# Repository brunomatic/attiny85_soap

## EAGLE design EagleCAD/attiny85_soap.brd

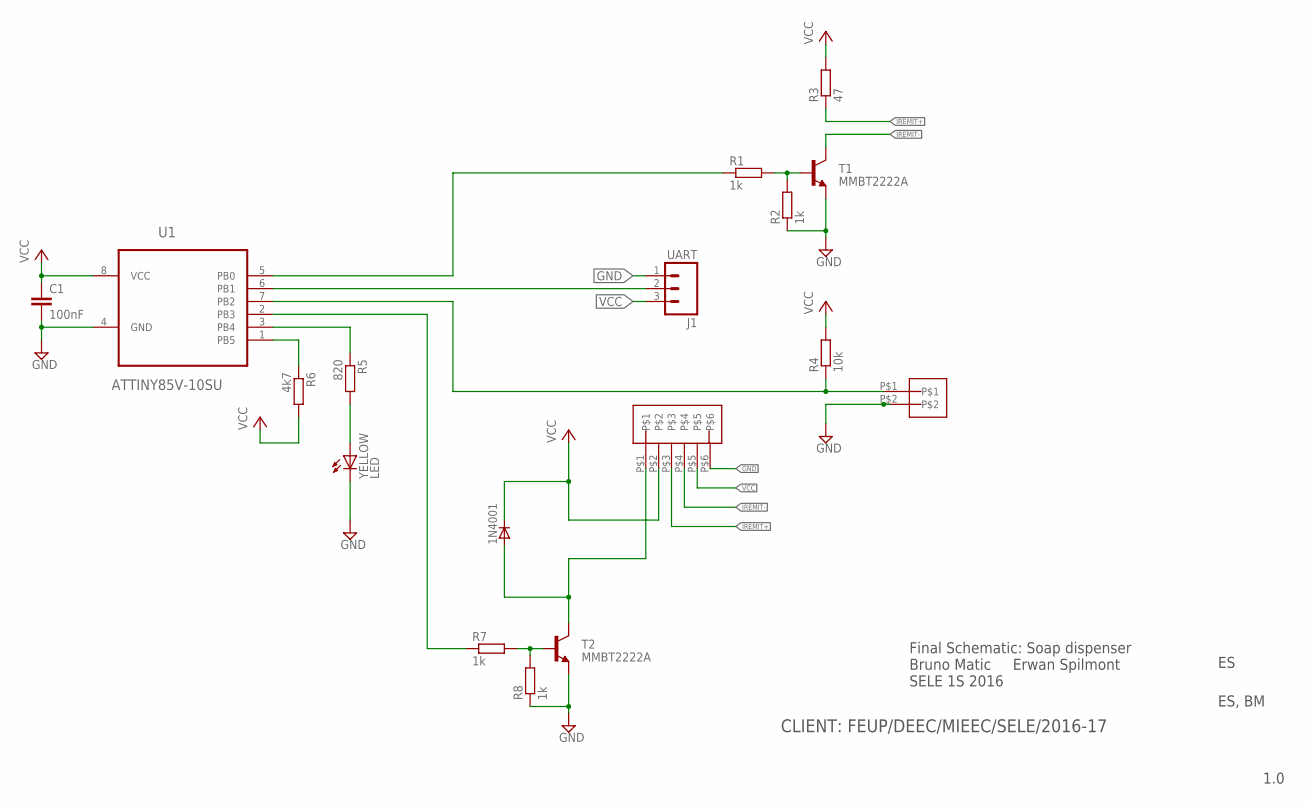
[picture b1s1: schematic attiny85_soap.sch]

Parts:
1N4001: SM400GENERIC; MELF-MLL41_DO213AB
C1: 100nF; C0603
IRDET_CON: 2_PIN_JST-XH
J1: UART; 1X03_NO_SILK
R1, R2, R7, R8: 1k; R0805
R3: 47; R0805
R4: 10k; R0805
R5: 820; R0805
R6: 4k7; R0805
T1, T2: MMBT2222A; SOT23-BEC
U1: ATTINY85V-10SU; SOIC127P798X216-8N
U$1: 6_PIN_JST-XH
YELLOW: LED; LED_LD260

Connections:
GND: C1.2, IRDET_CON.P$2, J1.1, R2.1, R8.1, T1.E, T2.E, U1.4 (GND), U$1.P$6, YELLOW.K (C)
IREMIT+: R3.1, U$1.P$3
IREMIT-: T1.C, U$1.P$4
IRRC+: IRDET_CON.P$1, R4.1, U1.7 (PB2)
unnamed: R6.1, U1.1 (PB5)
unnamed: R1.2, R2.2, T1.B
unnamed: R7.1, U1.2 (PB3)
unnamed: J1.2, U1.6 (PB1)
unnamed: R7.2, R8.2, T2.B
unnamed: R5.1, U1.3 (PB4)
unnamed: R1.1, U1.5 (PB0)
unnamed: R5.2, YELLOW.A
PUMP-: 1N4001.A, T2.C, U$1.P$1
VCC: 1N4001.C, C1.1, J1.3, R3.2, R4.2, R6.2, U1.8 (VCC), U$1.P$2, U$1.P$5

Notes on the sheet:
Final Schematic: Soap dispenser Bruno Matic Erwan Spilmont SELE 1S 2016
1.0
ES, BM
CLIENT: FEUP/DEEC/MIEEC/SELE/2016-17

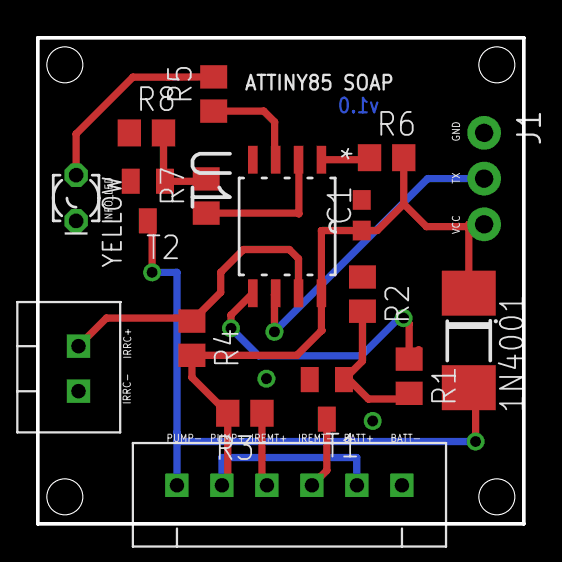
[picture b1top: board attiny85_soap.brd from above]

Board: 2 copper layers, 27.0 x 27.0 mm, 17 parts (0 on the bottom side), 14 nets.

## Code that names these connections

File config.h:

/*
 * config.h
 *
 *	This file contains all configurable parameters
 *
 *  Created on: 7. pro 2016.
 *      Author: Bruno
 */

#ifndef CONFIG_H_
#define CONFIG_H_

/**
 * General settings
 * IMPORTANT: one cycle = ~125ms (WDT is used for MCU wake ups to conserve battery)
 */
#define DEBUG 1										/* Debug levels: 3-highest(+EEPROM dumping) 0-no debug info */
#define HALT_ON_ERROR 1								/* Halt on system self test failure */
#define CLEAR_EEPROM 0								/* 1 - erases EEPROM usage data on startup, 0 - EEPROM intacted */
#define SN		0x00000001							/* Serial number of device stored in EEPROM at 0 */
#define CRC16	0xDF5E								/* CRC16 stored in EEPROM at location 4 */

/**
 *  Pin layout definition
 */
#define IR_EMITTER	PB0
#define UART		PB1								/* IMPORTANT: must be PB1 */
#define IR_DETECTOR	PB2
#define PUMP		PB3
#define INFO_LED	PB4

/*
 * SRAM memory parameters
 */
#define SRAM_START_ADR	96
#define SRAM_END_ADR	RAMEND

/*
 * Flash memory parameters
 */
#define FLASH_END	FLASHEND

/**
 * EEPROM memory and control settings
 */
#define EEPROM_SIZE	512								/* Size of MCU EEPROM in bytes */
#define PARAMETERS_EEPROM	2						/* Number of parameters periodically stored to EEPROM by EEPROM control */

/**
 * IR gate settings
 */
#define IR_GATE_DELAY 8								/* Delay between activating IR emitter and reading receiver in us */

/**
 * Pump settings
 */
#define PUMP_CYCLES 24								/* Pump active intervals, default: 24(~3 seconds) */
#define PUMP_WAIT_CYCLES 160						/* Pump reactivation wait time( between activations ), default: 160(~20 seconds) */

/**
 * Battery settings
 */
#define LOW_BATTERY_VOLTAGE 5000					/* Low battery warning - info led blinks if voltage below this */
#define MIN_OPERATING_VOLTAGE 4500					/* Below this voltage system shuts down */
#define BATTERY_CHECK_CYCLES 4800					/* Battery check period - default: 4800(~10 minutes) */

/**
 * Power save system settings
 */
#define POWER_SAVE_MODE	SLEEP_MODE_PWR_DOWN			/* MCU power save mode between wake ups */

/**
 * USI UART emulation
 */
#define BAUDRATE            19200					/* Possible baudrates at 8MHz: 9600bps or 19200bps */
#define STOPBITS            1						/* Number of stop bits */

/*
 * Timer0 parameters calculation for usage with USI to form UART
 */
#define CYCLES_PER_BIT       ( (F_CPU) / (BAUDRATE) )
#if (CYCLES_PER_BIT > 255)
#define DIVISOR             8
#define CLOCKSELECT         2
#else
#define DIVISOR             1
#define CLOCKSELECT         1
#endif
#define FULL_BIT_TICKS      ( (CYCLES_PER_BIT) / (DIVISOR) )

#endif /* CONFIG_H_ */

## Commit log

2016-12-10 Added basic memory tests; CRC in config not correct; restructured code
2016-12-12 Added basic sram tests
2016-12-13 Few fixes
2016-12-13 Commenting the code and some fixes
2016-12-17 Schematics and board

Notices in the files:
parts and their libraries:
SparkFun-Connectors: Licensing: Creative Commons ShareAlike 4.0 International - https://creativecommons.org/licenses/by-sa/4.0
